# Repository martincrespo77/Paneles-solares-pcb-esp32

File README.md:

# Seguidor Solar (Sun Tracker) de 2 Ejes con ESP32

**Cátedra:** Técnicas Digitales 2 — FIE (Facultad de Ingeniería del Ejército)  
**Plataforma:** ESP32 DOIT DevKit V1 (30 pines) · PlatformIO / Arduino C++  
**Estado:** Firmware implementado, compila sin warnings. Pendiente validación en banco.

---

## 1. Descripción

Migración del sistema de control de un **seguidor solar de dos ejes** (Azimut y Elevación) desde la plataforma original AVR (**ATmega168/328**, puente H L298HN y CD4053 — informe técnico *UNDEFI 263*) a un **ESP32**.

Se conservan las ecuaciones físicas del lazo, la calibración PI probada en el sistema original y la topología de sensado. Se agregan supervisión de seguridad, temporización determinística y una arquitectura de firmware mantenible.

---

## 2. Arquitectura

```
          [ 4 LDR en cruz: F0 F1 / F2 F3 ]   (divisor LDR + 4k7)
                         |
                         v
          [ ADC1 ESP32 — 8 muestras, calibrado, escala 10 bits ]
                         |
                         v
          [ Supervisión: TRACKING / NIGHT / SENSOR_FAULT ]
                         |
                         v
          [ Error Azimut / Elevación ]
                         |
                         v
          [ PI por eje + anti-windup + zona muerta ]
                         |
                         v
          [ PWM LEDC 1 kHz / 10 bits + sentido (tiempo muerto) ]
                         |
                         v
          [ Puente H doble (L298N) ]
                         |
                         v
          [ Motor DC Azimut ]   [ Motor DC Elevación ]
```

### Ley de control

| Paso | Ecuación / valor |
|---|---|
| Error elevación | `e_El = (F2 + F3 − F0 − F1) / 2` (inferior − superior) |
| Error azimut | `e_Az = (F1 + F3 − F0 − F2) / 2` (derecha − izquierda) |
| Zona muerta | `abs(e) ≤ 5` → motor parado, integrador en 0 |
| Integrador | `I[k] = sat(I[k−1] + e[k], ±400)` |
| Acción | `u[k] = Kp·e[k] + Ki·I[k]`, con `Kp = 5.0`, `Ki = 0.1` (por muestra) |
| Salida | `PWM = min(abs(u), 1023)`, sentido = signo de `u` |
| Período | `Ts = 20 ms` (50 Hz) → `Ki` continuo equivalente = 5 s⁻¹ |

### Fail-safes

| Condición | Detección | Acción |
|---|---|---|
| Noche / oscuridad | Promedio LDR < 40 cuentas durante 10 s (sale con > 80) | Motores parados, LED destello corto |
| LDR desconectado | Un LDR < 10 cuentas con luz ambiente, 200 ms | Motores parados, LED fijo |
| Inversión de giro | Cambio de signo de `u` | PWM = 0 durante 40 ms antes de invertir |
| Final de carrera | Opcional (`USE_LIMIT_SWITCHES`) | Bloquea el sentido activado |
| Cuelgue del firmware | Watchdog del `loop()` | Reset → arranque con motores parados |

Todos los umbrales están en [`include/config.h`](include/config.h).

---

## 3. Mapeo de pines (ESP32 DevKit V1)

| Señal | Pin | Función | Destino |
|---|:---:|---|---|
| FOTO0 | `GPIO36` (VP) | ADC1_CH0 | LDR superior izquierdo |
| FOTO1 | `GPIO39` (VN) | ADC1_CH3 | LDR superior derecho |
| FOTO2 | `GPIO34` | ADC1_CH6 | LDR inferior izquierdo |
| FOTO3 | `GPIO35` | ADC1_CH7 | LDR inferior derecho |
| PWM_AZ | `GPIO25` | LEDC CH0 | ENA — motor Azimut |
| PWM_EL | `GPIO26` | LEDC CH1 | ENB — motor Elevación |
| DIR_AZ | `GPIO27` | Digital | Sentido Azimut |
| DIR_EL | `GPIO14` | Digital | Sentido Elevación |
| STATUS | `GPIO2` | Digital | LED onboard |

Solo se usa **ADC1** (el ADC2 queda inutilizable con WiFi activo) y ningún strapping pin crítico. Se recomienda pull-down de 10 kΩ en ENA/ENB para garantizar motores parados durante el boot.

> **L298N:** cada motor necesita IN1/IN2 complementarios. Con un único pin de sentido por motor hace falta un inversor (en el diseño original lo resolvía el CD4053).

---

## 4. Estructura del repositorio

```
├── platformio.ini              Configuración de compilación (platform fijada)
├── include/config.h            Pines, ganancias, tiempos y umbrales
├── src/main_tracker.cpp        Firmware del tracker
├── Kicad/Control de panel/     Esquemático y PCB (KiCad), zócalo DevKit 30 pines
│   └── lib/                    Símbolo y footprint ESP32_DEVKIT_V1_30PIN
└── docs/
    ├── CONTEXTO_TD2_SUN_TRACKER.md          Referencia única: contexto y trazabilidad
    ├── DOCUMENTO_TECNICO_TD2_SUN_TRACKER.md Especificación técnica y modelo
    ├── PLANMODE_ARMADO_TD2.md               Puesta en marcha en banco por etapas
    ├── img/                                 Imágenes y diagramas
    └── legacy/                              Sistema AVR original (solo referencia)
        ├── UNDEFI 263 - Informe Final.pdf
        ├── circuito/Sun_seeker.PDF
        └── firmware_avr/                    Fuentes C del ATmega (popo.c, PID_*.c…)
```

---

## 5. Compilación y carga

Requiere [PlatformIO](https://platformio.org/) (extensión de VS Code o CLI). Ajustar `upload_port` / `monitor_port` en `platformio.ini` al puerto COM de la placa.

```powershell
pio run -e tracker                  # compilar
pio run -e tracker -t upload        # cargar
pio device monitor -e tracker       # monitor serie a 115200 baud
```

Si la placa no entra sola en modo descarga, usar `-e tracker_manual` y mantener presionado **BOOT** al iniciar la carga.

---

## 6. Puesta en marcha

1. **Sin motores:** cargar el firmware y abrir el monitor. Verificar el banner de boot.
2. **Sensores:** sombrear cada LDR por separado y comprobar que baja solo su canal `F`.
3. **Signo del error:** iluminar desde abajo → `eEl` positivo; desde la derecha → `eAz` positivo.
4. **Fail-safes:** desconectar un LDR → `[STATE] TRACK -> FAULT`; tapar todos 10 s → `NIGHT`.
5. **Motores en vacío:** confirmar que cada eje gira hacia la luz. Si gira al revés, invertir `DIR_*_POSITIVE_LEVEL` en `config.h`.
6. **Sintonía:** ajustar `DEAD_BAND`, `KP_*`, `KI_*` según la mecánica real.

Formato de telemetría (cada 500 ms):

```
[   12500] TRACK F= 512  530  498  515 | eAz= +17.5 eEl=  -14.5 | iAz= +35.0 iEl= -29.0 | pwmAz=+  91 pwmEl=-  75 | ovr=0
```

Guía detallada: [`docs/PLANMODE_ARMADO_TD2.md`](docs/PLANMODE_ARMADO_TD2.md).

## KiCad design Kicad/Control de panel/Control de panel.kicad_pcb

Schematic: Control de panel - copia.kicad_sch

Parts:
C1, C4, C5: 0.1u; C_Disc_D6.0mm_W2.5mm_P5.00mm
C2: 1u; CP_Radial_D6.3mm_P2.50mm
C3: 10u; CP_Radial_D6.3mm_P2.50mm
C6: 100u; CP_Radial_D6.3mm_P2.50mm
D1, D2, D3, D4, D5, D6, D7, D8, D10: 1N5822; D_DO-201AD_P15.24mm_Horizontal
J1: Output MOTORA; TerminalBlock_Phoenix_PT-1,5-2-5.0-H_1x02_P5.00mm_Horizontal
J2: Output MOTORB; TerminalBlock_Phoenix_PT-1,5-2-5.0-H_1x02_P5.00mm_Horizontal
J5: Input 9v; TerminalBlock_Phoenix_PT-1,5-2-5.0-H_1x02_P5.00mm_Horizontal
J8: Conn_01x05_Pin; PinHeader_1x05_P2.00mm_Vertical
R1, R2, R3, R4: 4k7; R_Axial_DIN0207_L6.3mm_D2.5mm_P10.16mm_Horizontal
R5, R6, R7, R8, R9, R10, R11, R12: R; R_Axial_DIN0207_L6.3mm_D2.5mm_P10.16mm_Horizontal
U1: L298N; TO-220-15_P2.54x5.08mm_StaggerOdd_Lead4.58mm_Vertical
U2: LM7805_TO220; TO-220-3_Vertical
U4: DEVKIT_V1_ESP32-WROOM-32; MODULE_DEVKIT_V1_ESP32-WROOM-32; PARTREV N/A
U5: CNY74-4H; DIL16; MPN CNY74-4H
U6: ESP32_DEVKIT_V1_30PIN

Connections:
/Vcc 5v: C1.1, C3.1, C5.1, U1.6 (EnA), U1.9 (Vss), U1.11 (EnB), U2.3 (VO), U4.19 (EXT_5V), U5.10, U5.11, U5.14, U5.15
GND: C1.2, C2.2, C3.2, C4.2, C5.2, C6.2, D3.2 (A), D4.2 (A), D5.2 (A), D7.2 (A), J5.1, R1.2, R2.2, R3.2, R4.2, R5.1, R6.2, R7.2, R8.2, U1.1 (SENSE_A), U1.8 (GND), U1.15 (SENSE_B), U2.2 (GND), U4.14 (GND1), U4.32 (GND2), U5.3, U5.6, U5.7
unnamed: D1.2 (A), D4.1 (K), J1.1, U1.2 (OUT1)
unnamed: C2.1, C4.1, C6.1, D1.1 (K), D2.1 (K), D6.1 (K), D8.1 (K), D10.1 (K), U1.4 (Vs), U2.1 (VI)
unnamed: D2.2 (A), D3.1 (K), J1.2, U1.3 (OUT2)
unnamed: D5.1 (K), D6.2 (A), J2.2, U1.13 (OUT3)
unnamed: D7.1 (K), D8.2 (A), J2.1, U1.14 (OUT4)
unnamed: D10.2 (A), J5.2
unnamed: J8.1, U4.1 (3V3)
unnamed: J8.2, R4.1, U4.6 (IO35)
unnamed: J8.3, R3.1, U4.5 (IO34)
unnamed: J8.4, R2.1, U4.4 (SENSOR_VN)
unnamed: J8.5, R1.1, U4.3 (SENSOR_VP)
unnamed: R9.1, U5.1
unnamed: R10.1, U5.4
unnamed: R11.1, U5.5
unnamed: R12.1, U5.8
unnamed: R8.1, U1.5 (IN1), U5.9
unnamed: R7.1, U1.7 (IN2), U5.12
unnamed: R6.1, U1.10 (IN3), U5.13
unnamed: R5.2, U1.12 (IN4), U5.16
unnamed: R12.2, U4.27 (IO16)
unnamed: R11.2, U4.28 (IO17)
unnamed: R10.2, U4.30 (IO18)
unnamed: R9.2, U4.31 (IO19)

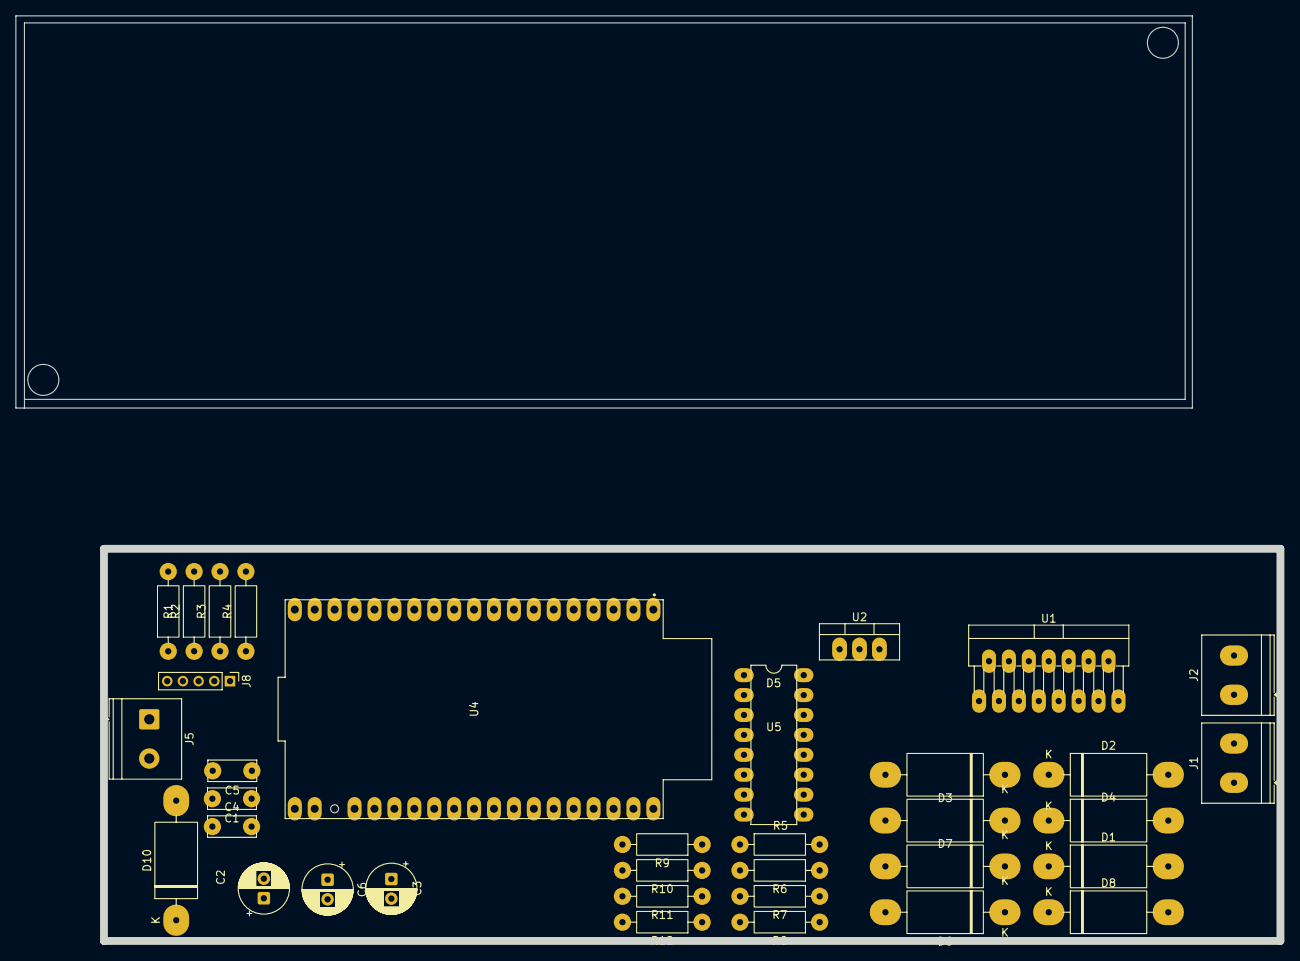
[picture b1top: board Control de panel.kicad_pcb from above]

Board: 2 copper layers, 150.0 x 50.0 mm, 35 parts (0 on the bottom side), 25 nets, no tracks yet.
